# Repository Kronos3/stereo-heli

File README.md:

# stereo-heli
Stereo Vision Quadcopter

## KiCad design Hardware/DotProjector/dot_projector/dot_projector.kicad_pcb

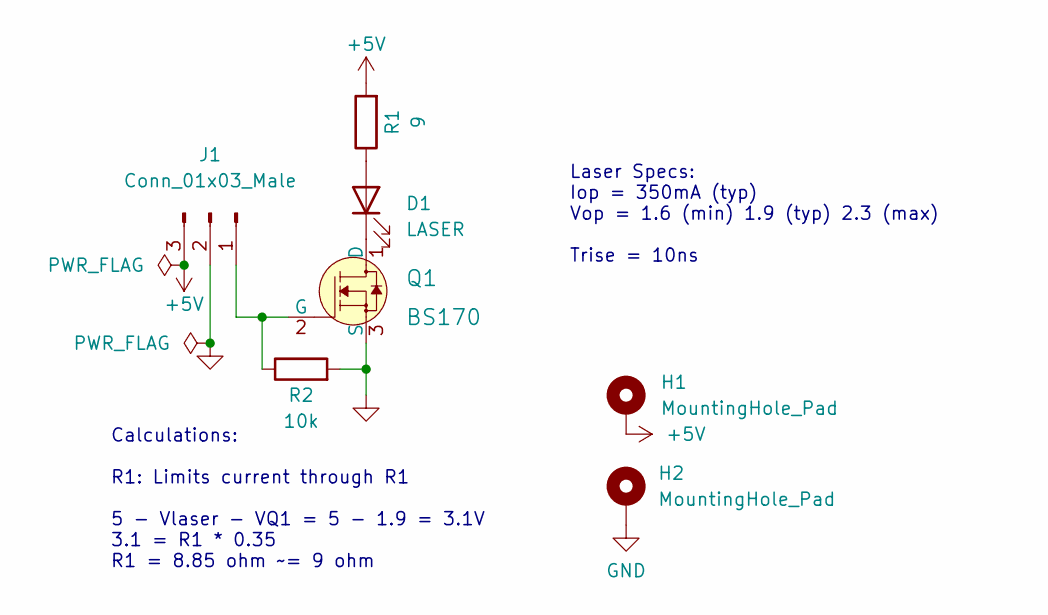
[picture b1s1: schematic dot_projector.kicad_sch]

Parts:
D1: LASER; BELICE-850
H1, H2: MountingHole_Pad; MountingHole_2.2mm_M2_DIN965_Pad
J1: Conn_01x03_Male; PinHeader_1x03_P2.54mm_Vertical
Q1: BS170; TO-92-3; MPN BS170; Digi-Key_PN BS170-ND
R1: 9; R_Axial_DIN0309_L9.0mm_D3.2mm_P12.70mm_Horizontal
R2: 10k; R_0603_1608Metric

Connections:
+5V: H1.1, J1.3, R1.2
GND: H2.1, J1.2, Q1.3 (S), R2.2
unnamed: D1.1 (K), Q1.1 (D)
unnamed: D1.2 (A), R1.1
unnamed: J1.1, Q1.2 (G), R2.1

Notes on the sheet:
Calculations: R1: Limits current through R1 5 - Vlaser - VQ1 = 5 - 1.9 = 3.1V 3.1 = R1 * 0.35 R1 = 8.85 ohm ~= 9 ohm
Laser Specs: Iop = 350mA (typ) Vop = 1.6 (min) 1.9 (typ) 2.3 (max) Trise = 10ns

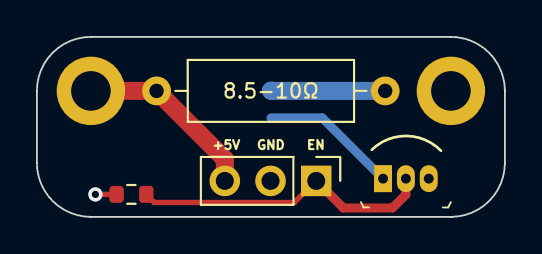
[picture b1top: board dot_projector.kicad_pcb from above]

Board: 2 copper layers, 26.0 x 10.0 mm, 7 parts (1 on the bottom side), 5 nets.

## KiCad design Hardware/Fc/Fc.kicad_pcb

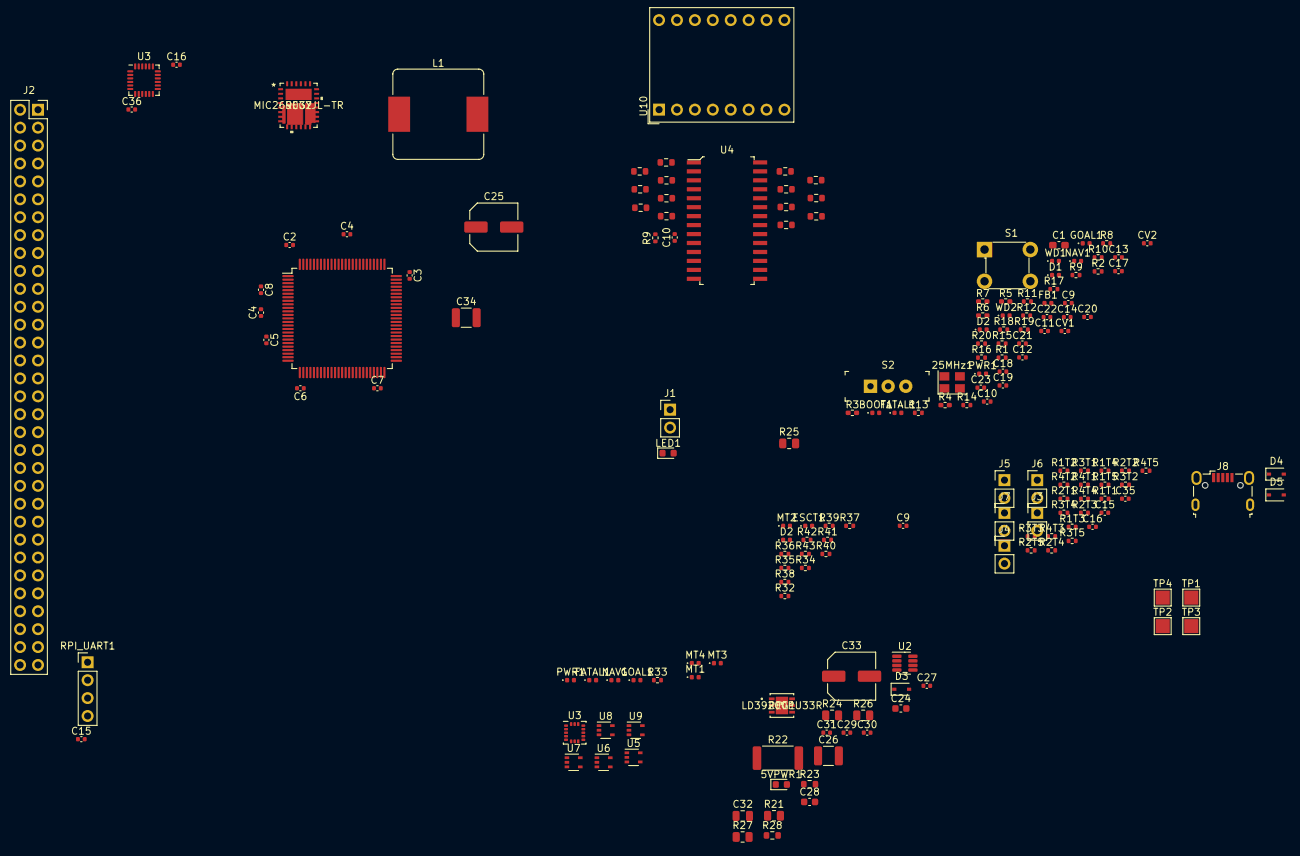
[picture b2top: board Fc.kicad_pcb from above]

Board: 4 copper layers, 173 parts (0 on the bottom side), 114 nets, no tracks yet.

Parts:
5VPWR1: G; LED_0603_1608Metric
25MHz1: HSE1; Crystal_SMD_Abracon_ABM8G-4Pin_3.2x2.5mm
BOOT1: R; LED_0402_1005Metric
C1: 10u; C_0603_1608Metric_Pad1.08x0.95mm_HandSolder
C2, C3, C4, C4#2, C5, C6, C7, C8, C9#2, C10, C11, C12, C13, C14, C18, C19, C21, C29, C30, C31: 100n; C_0402_1005Metric
C9, C17, C20: 1u; C_0402_1005Metric
C10#2, C15, C15#2, C35: 0.1u; C_0402_1005Metric
C16: 0.1p; C_0402_1005Metric
C16#2, C27: 2u2; C_0402_1005Metric
C22, C23: 10p; C_0402_1005Metric
C24, C28: 10u; C_0603_1608Metric
C25, C33: 100u; C_Elec_6.3x7.7
C26, C34: 47u; C_1210_3225Metric
C32: 4n7; C_0805_2012Metric
C36: 2n2; C_0402_1005Metric
CV1, CV2: 2u2; C_0402_1005Metric
D1: STAT; LED_0402_1005Metric
D2, D2#2: BAT; LED_0402_1005Metric
D3, D4, D5: SD103AWS; D_SOD-323
ESCT1: R; LED_0402_1005Metric
FATAL1, FATAL1#2: R; LED_0402_1005Metric
FB1: 120R; L_0402_1005Metric
GOAL1, GOAL1#2: G; LED_0402_1005Metric
J1: PWR; PinHeader_1x02_P2.54mm_Vertical
J2: Raspberry_Pi_2_3; PinSocket_2x32_P2.54mm_Vertical
J3, J4, J5, J6, J7: Conn_01x02_Male; PinHeader_1x02_P2.54mm_Vertical
J8: USB_B_Micro; USB_Micro-B_Wuerth_629105150521
L1: 15u; L_Bourns_SRP1245A
LED1: G; LED_0603_1608Metric
MT1, MT2, MT3, MT4: R; LED_0402_1005Metric
NAV1, NAV1#2: G; LED_0402_1005Metric
PWR1, PWR1#2: R; LED_0402_1005Metric
R1, R2: 4k7; R_0402_1005Metric
R1T1, R1T2, R1T3, R1T4, R1T5: 6k02; R_0402_1005Metric
R2T1, R2T2, R2T3, R2T4, R2T5, R3T1, R3T2, R3T3, R3T4, R3T5: 7k7; R_0402_1005Metric
R3, R4: 4k7; R_0402_1005Metric_Pad0.72x0.64mm_HandSolder
R4T1, R4T2, R4T3, R4T4, R4T5: 1k5; R_0402_1005Metric
R5: 47; R_0402_1005Metric_Pad0.72x0.64mm_HandSolder
R6: 10k; R_0402_1005Metric_Pad0.72x0.64mm_HandSolder
R7: 620; R_0402_1005Metric_Pad0.72x0.64mm_HandSolder
R8, R9, R11, R12#2, R14#2, R15, R16, R17, R20#2, R32, R34, R35, R37, R38, R39, R40, R43: 1k; R_0402_1005Metric
R9#2: 10k; R_0402_1005Metric
R10, R13#2, R18, R19#2, R33, R36, R41, R42: 2k2; R_0402_1005Metric
R10#2, R11#2, R12, R13, R14, R15#2, R16#2, R17#2, R18#2, R19, R20, R29, R30, R31: 150R; R_0603_1608Metric
R21, R24: 10k; R_0805_2012Metric
R22: 10m; R_2512_6332Metric
R23: 240; R_0603_1608Metric
R25, R26: 6k8; R_0805_2012Metric
R27: 1k3; R_0805_2012Metric
R28: 560; R_0603_1608Metric
REG1: LD39200PU33R
REG2: MIC26903YJL-TR
RPI_UART1: Conn_01x04_Male; PinHeader_1x04_P2.54mm_Vertical
S1: 1825910-6; Switch_Tactile_THT_6x6mm
S2: EG1218; Switch_Slide_11.6x4mm_EG1218
TP1: VBAT; TestPoint_Pad_2.0x2.0mm
TP2: +5V; TestPoint_Pad_2.0x2.0mm
TP3: +3V3; TestPoint_Pad_2.0x2.0mm
TP4: GND; TestPoint_Pad_2.0x2.0mm
U1: STM32F407VGTx; LQFP-100_14x14mm_P0.5mm
U2: INA219AIDCNR; SOT-23-8
U3: ICM-20602; LGA-16_3x3mm_P0.5mm_LayoutBorder3x5y
U3#2: MPU-6000; InvenSense_QFN-24_4x4mm_P0.5mm
U4: MCP23017-E_SO; SOIC-28_W7.5mm
U5, U6, U7, U8, U9: TLV9001IDCK; SOT-353_SC-70-5
U10: DA04-11SURKWA
WD1, WD2: R; LED_0402_1005Metric

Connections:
5VBAT: 5VPWR1.2 (A), C32.1, C33.1, C34.1, D5.2 (A), L1.2, R26.1
+3V3: C1.1, C2.1, C3.1, C4.1, C4#2.1, C5.1, C6.1, C7.1, C8.1, C9.1, C9#2.1, C10.1, C10#2.2, C11.1, C12.1, C13.1, C14.1, C15.2, C15#2.1, C16#2.1, C28.1, C30.1, FB1.2, J3.2, J4.2, J5.2, J6.2, J7.2, LED1.2 (A), PWR1.2 (A), PWR1#2.2 (A), R1.1, R2.1, R3.1, R3T1.1, R3T2.1, R3T3.1, R3T4.1, R3T5.1, R4.1, R9#2.1, REG1.1 (OUT), REG1.2 (ADJ/SENSE), S2.3, TP3.1, U1.6 (VBAT), U1.11 (VDD), U1.19 (VDD), U1.28 (VDD), U1.50 (VDD), U1.75 (VDD), U1.100 (VDD), U2.4 (VS), U3.1 (VDDIO), U3.16 (VDD), U3#2.13 (VDD), U4.9 (VDD), U5.5 (V+), U6.5 (V+), U7.5 (V+), U8.5 (V+), U9.5 (V+), U10.4 (DIG1_CA), U10.5 (DIG2_CA)
+5V: C24.1, D4.1 (K), D5.1 (K), J2.2 (5V), J2.4 (5V), REG1.5 (EN), REG1.6 (IN), RPI_UART1.1, TP2.1
BOOT0: R6.1, U1.94 (BOOT0)
GND: 25MHz1.2, 25MHz1.4, BOOT1.1 (K), C1.2, C2.2, C3.2, C4.2, C4#2.2, C5.2, C6.2, C7.2, C8.2, C9.2, C9#2.2, C10.2, C10#2.1, C11.2, C12.2, C13.2, C14.2, C15.1, C15#2.2, C16.2, C16#2.2, C17.2, C18.2, C19.2, C20.2, C21.2, C22.2, C23.2, C24.2, C25.2, C26.2, C27.2, C28.2, C30.2, C32.2, C33.2, C34.2, C35.2, C36.2, CV1.2, CV2.2, ESCT1.1 (K), FATAL1.1 (K), FATAL1#2.1 (K), GOAL1.1 (K), GOAL1#2.1 (K), J1.2, J2.6 (GND), J2.9 (GND), J2.14 (GND), J2.20 (GND), J2.25 (GND), J2.30 (GND), J2.34 (GND), J2.39 (GND), J8.5 (GND), MT1.1 (K), MT2.1 (K), MT3.1 (K), MT4.1 (K), NAV1.1 (K), NAV1#2.1 (K), R1T1.2, R1T2.2, R1T3.2, R1T4.2, R1T5.2, R2T1.2, R2T2.2, R2T3.2, R2T4.2, R2T5.2, R20#2.2, R23.1, R27.2, R28.1, R43.2, REG1.3 (GND), REG1.7 (GND), REG2.2 (PGND), REG2.5 (PGND), REG2.6 (PGND), REG2.7 (PGND), REG2.8 (PGND), REG2.21 (PGND), REG2.23 (SGND), RPI_UART1.2, S1.3, S1.4, S2.1, TP4.1, U1.10 (VSS), U1.20 (VSSA), U1.27 (VSS), U1.74 (VSS), U1.99 (VSS), U2.3 (GND), U2.7 (A0), U2.8 (A1), U3.5 (~CS), U3.8 (FSYNC), U3.9 (GND), U3.10 (GND), U3.11 (GND), U3.12 (GND), U3.13 (GND), U3.15 (GND), U3#2.8 (~CS), U3#2.18 (GND), U4.10 (VSS), U4.15 (A0), U4.16 (A1), U4.17 (A2), U5.2 (V-), U6.2 (V-), U7.2 (V-), U8.2 (V-), U9.2 (V-), WD1.1 (K), WD2.1 (K)
HSE_IN: 25MHz1.1, C22.1, U1.12 (PH0)
HSE_OUT: R7.1, U1.13 (PH1)
I2C1_SCL: R1.2, U1.92 (PB6), U4.12 (SCK)
I2C1_SDA: R2.2, U1.93 (PB7), U4.13 (SDA)
I2C3_SCL: R3.2, U1.67 (PA8), U2.5 (SCL)
I2C3_SDA: R4.2, U1.66 (PC9), U2.6 (SDA)
INT0: U1.57 (PD10), U3.6 (INT), U3#2.12 (INT)
LED1: R9.1, R32.1, U1.97 (PE0)
LED2: R10.1, R33.1, U1.98 (PE1)
LED3: R11.1, R34.1, U1.1 (PE2)
LED4: R15.1, R38.1, U1.2 (PE3)
LED5: R16.1, R39.1, U1.3 (PE4)
LED6: R17.1, R40.1, U1.4 (PE5)
LED7: R18.1, R41.1, U1.5 (PE6)
LED8: R19#2.1, R42.1, U1.7 (PC13)
NRST: C19.1, S1.1, S1.2, U1.14 (NRST)
unnamed: 5VPWR1.1 (K), R28.2
unnamed: 25MHz1.3, C23.1, R7.2
unnamed: BOOT1.2 (A), R8.2
unnamed: C16.1, U3#2.10 (REGOUT)
unnamed: C31.2, R25.1
unnamed: C35.1, U3.14 (REGOUT)
unnamed: C36.1, U3#2.20 (CPOUT)
unnamed: CV1.1, U1.49 (VCAP_1)
unnamed: CV2.1, U1.73 (VCAP_2)
unnamed: D1.1 (BA), R11.2
unnamed: D1.2 (GA), R10.2
unnamed: D2.1 (BA), D2#2.1 (BA), R14#2.2, R37.2
unnamed: D2.2 (GA), D2#2.2 (GA), R13#2.2, R36.2
unnamed: R12#2.2, R35.2
unnamed: ESCT1.2 (A), R39.2
unnamed: FATAL1.2 (A), FATAL1#2.2 (A), R15.2, R40.2
unnamed: GOAL1.2 (A), GOAL1#2.2 (A), R18.2, R41.2
unnamed: J2.8 (GPIO14/TXD), RPI_UART1.3
unnamed: J2.10 (GPIO15/RXD), RPI_UART1.4
unnamed: LED1.1 (K), R23.2
unnamed: MT1.2 (A), R32.2
unnamed: MT2.2 (A), R33.2
unnamed: MT3.2 (A), R34.2
unnamed: MT4.2 (A), R38.2
unnamed: NAV1.2 (A), NAV1#2.2 (A), R19#2.2, R42.2
unnamed: PWR1.1 (K), PWR1#2.1 (K), R20#2.1, R43.1
unnamed: R2T1.1, R3T1.2, R4T1.1, U5.3 (-)
unnamed: R2T2.1, R3T2.2, R4T2.1, U6.3 (-)
unnamed: R2T3.1, R3T3.2, R4T3.1, U7.3 (-)
unnamed: R2T4.1, R3T4.2, R4T4.1, U8.3 (-)
unnamed: R2T5.1, R3T5.2, R4T5.1, U9.3 (-)
unnamed: R6.2, R8.1, S2.2
unnamed: R10#2.1, U4.1 (GPB0)
unnamed: R10#2.2, U10.15 (DIG1_A)
unnamed: R11#2.1, U4.2 (GPB1)
unnamed: R11#2.2, U10.13 (DIG1_B)
unnamed: R12.1, U4.3 (GPB2)
unnamed: R12.2, U10.1 (DIG1_C)
unnamed: R13.1, U4.4 (GPB3)
unnamed: R13.2, U10.3 (DIG1_D)
unnamed: R14.1, U4.5 (GPB4)
unnamed: R14.2, U10.2 (DIG1_E)
unnamed: R15#2.1, U4.6 (GPB5)
unnamed: R15#2.2, U10.14 (DIG1_F)
unnamed: R16#2.1, U4.7 (GPB6)
unnamed: R16.2, R16#2.2, U10.16 (DIG1_G), WD1.2 (A)
unnamed: R17#2.1, U10.10 (DIG2_A)
unnamed: R17.2, R17#2.2, U4.21 (GPA0), WD2.2 (A)
unnamed: R18#2.1, U10.12 (DIG2_B)
unnamed: R18#2.2, U4.22 (GPA1)
unnamed: R19.1, U10.8 (DIG2_C)
unnamed: R19.2, U4.23 (GPA2)
unnamed: R20.1, U10.6 (DIG2_D)
unnamed: R20.2, U4.24 (GPA3)
unnamed: R29.1, U10.7 (DIG2_E)
unnamed: R29.2, U4.25 (GPA4)
unnamed: R30.1, U10.11 (DIG2_F)
unnamed: R30.2, U4.26 (GPA5)
unnamed: R31.1, U10.9 (DIG2_G)
unnamed: R31.2, U4.27 (GPA6)
unnamed: R9#2.2, U4.18 (~RESET)
REG_BST: C29.1, D3.1 (K), REG2.20 (BST)
REG_CS: C29.2, C31.1, L1.1, REG2.4 (SW), REG2.9 (SW), REG2.10 (SW), REG2.11 (SW), REG2.12 (SW), REG2.22 (CS)
REG_EN: R21.2, REG2.26 (EN)
REG_FB: R25.2, R26.2, R27.1, REG2.24 (FB)
REG_PG: R24.2, REG2.25 (PG)
REG_VDD: C27.1, D3.2 (A), R24.1, REG2.1 (PVDD), REG2.28 (VDD)
REG_VIN: C25.1, C26.1, R21.1, R22.1, REG2.13 (PVIN), REG2.14 (PVIN), REG2.15 (PVIN), REG2.16 (PVIN), REG2.17 (PVIN), REG2.18 (PVIN), REG2.19 (PVIN), REG2.27 (VIN), TP1.1, U2.2 (IN-)
SPI2_MISO: J2.21 (MISO0/GPIO9), U1.17 (PC2)
SPI2_MOSI: J2.19 (MOSI0/GPIO10), U1.18 (PC3)
SPI2_SCK: J2.23 (SCLK0/GPIO11), U1.72 (PA13)
SPI3_MISO: U1.79 (PC11), U3.4 (SAO/SD0), U3#2.9 (AD0/MISO)
SPI3_MOSI: U1.91 (PB5), U3.3 (SDA/SDI), U3#2.24 (SDA/MOSI)
SPI3_SCK: U1.78 (PC10), U3.2 (SCL/SPC), U3#2.23 (SCL/SCLK)
T1: J3.1, R1T1.1, U5.1 (+)
T2: J4.1, R1T2.1, U6.1 (+)
T3: J5.1, R1T3.1, U7.1 (+)
T4: J6.1, R1T4.1, U8.1 (+)
T5: J7.1, R1T5.1, U9.1 (+)
THRM1: R4T1.2, U1.23 (PA0), U5.4
THRM2: R4T2.2, U1.24 (PA1), U6.4
THRM3: R4T3.2, U1.25 (PA2), U7.4
THRM4: R4T4.2, U1.35 (PB0), U8.4
THRM5: R4T5.2, U1.34 (PC5), U9.4
TIM1_CH1: R12#2.1, R35.1, U1.40 (PE9)
TIM1_CH2: R13#2.1, R36.1, U1.42 (PE11)
TIM1_CH3: R14#2.1, R37.1, U1.44 (PE13)
USB_D+: J8.3 (D+), U1.71 (PA12)
USB_D-: J8.2 (D-), U1.70 (PA11)
VBAT: J1.1, R22.2, U2.1 (IN+)
VBUS: D4.2 (A), J8.1 (VBUS)
VDDA: C17.1, C18.1, FB1.1, R5.1, U1.22 (VDDA)
VREF+: C20.1, C21.1, R5.2, U1.21 (VREF+)

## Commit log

2022-11-02 Started schematic for flight controller
2022-11-02 Added USB
2022-11-04 Added camera implementation and basic Top
2022-11-20 Building with new libcamera updates
2022-11-20 Stereo support
2022-11-20 Wire up the frame pipelines
2022-11-21 Booting FSW
2022-11-21 Added comms
2022-11-23 Remove fprime to readd
2022-11-23 Connecting to GDS
2022-11-23 Build on macOS
2022-12-03 Working camera streaming, added testing notebook
2022-12-14 Added cadre interaction for testing
2023-01-17 Implemented Fc, Sapp, and Joystick
2023-01-20 Update to new libcamera
2023-01-20 Various Fc fixes
2023-01-21 Use linux timer instead of block driver
2023-01-21 Command enable/disable of Fc uart lines
2023-01-22 Working comm link between Fc and Pi
2023-01-22 Fixing ident
2023-01-22 Added Fc telemetry
2023-01-22 Added fc testing
2023-01-29 Working joystick
2023-01-29 Add missing field to contrustor
2023-01-29 Clean up joystick mapping
2023-01-30 Support inverted axis on joystick
2023-02-23 Image saving in video streamer, updated to libcamera 0.0.3
2023-02-23 Added cam test nb
2023-02-25 Working camera calibration
2023-02-25 Remove useless sequences
2023-02-26 Working camera calibration, added dot projector pcb
2023-02-26 Exported step
2023-03-05 Added SLAM library
2023-03-05 Reformat
2023-03-05 Started libparallel
2023-03-05 Parallelize vision processing
2023-03-05 Allow labelling process jobs with token
2023-03-05 Cleanup parallel code
2023-03-14 Wrote a frame manager
2023-03-14 Use 4x4 homogeneous transformation matrix
2023-03-14 Cleanup fm.GET
2023-03-14 Clean up tform code
2023-03-29 Started Vo code
2023-04-03 Sync my fprime updates

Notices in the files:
parts and their libraries:
Copyright 2021 Accelerated Designs. All rights reserved.
